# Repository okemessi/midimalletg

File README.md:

Wiki: https://github.com/okemessi/midimalletg/wiki

# midimalletg

Midimalletg is a MIDI mallet controller for marimba/other keyboard percussion players. This project is developed as a hobby and personal project by okemessi. It is provided as-is because it is still under development. 

## Specifications

Detailed specifications will be added to the wiki page (https://github.com/okemessi/midimalletg/wiki) as they become available.

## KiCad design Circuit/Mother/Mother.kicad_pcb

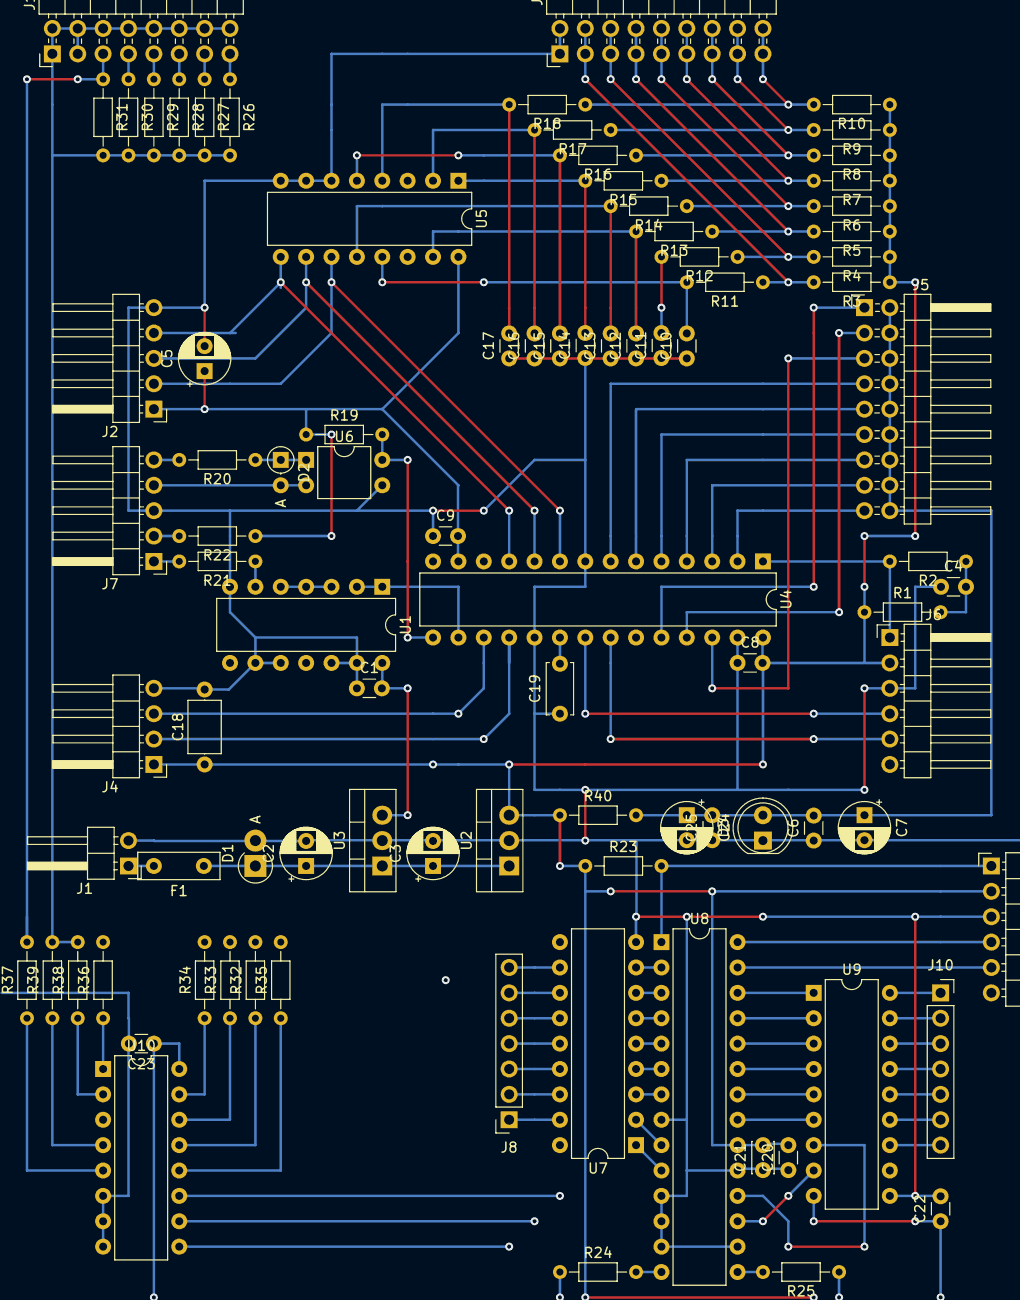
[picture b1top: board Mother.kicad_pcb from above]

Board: 4 copper layers, 90 parts (0 on the bottom side), 98 nets.

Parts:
C1, C4, C6, C8, C9, C10, C11, C12, C13, C14, C15, C16, C17, C20, C22, C23, C25: 0.1u; C_Disc_D3.0mm_W1.6mm_P2.50mm
C2, C3, C5, C7, C24: 10u; CP_Radial_D5.0mm_P2.50mm
C18: 10u; C_Axial_L5.1mm_D3.1mm_P7.50mm_Horizontal
C19: 10uF; C_Disc_D5.0mm_W2.5mm_P5.00mm
C21: 0.01u; C_Disc_D3.0mm_W2.0mm_P2.50mm
D1: 1N4007; D_DO-41_SOD81_P2.54mm_Vertical_AnodeUp
D2: 1SS178; D_DO-35_SOD27_P2.54mm_Vertical_AnodeUp
D3: LED; LED_D5.0mm
F1: RXEF050; C_Disc_D8.0mm_W2.5mm_P5.00mm
J1: Conn_01x02_Male; PinHeader_1x02_P2.54mm_Horizontal
J2, J7: Conn_01x05_Male; PinHeader_1x05_P2.54mm_Horizontal
J3, J5: Conn_02x09_Odd_Even; PinHeader_2x09_P2.54mm_Horizontal
J4: Conn_01x04_Male; PinHeader_1x04_P2.54mm_Horizontal
J6, J9: Conn_PIC_ICSP_ICD; PinHeader_1x06_P2.54mm_Horizontal
J8, J10: Conn_01x07_Female; PinSocket_1x07_P2.54mm_Vertical
J11: Conn_02x08_Odd_Even; PinHeader_2x08_P2.54mm_Horizontal
R1, R3, R4, R5, R6, R7, R8, R9, R10, R11, R12, R13, R14, R15, R16, R17, R18, R23: 10k; R_Axial_DIN0204_L3.6mm_D1.6mm_P7.62mm_Horizontal
R2, R40: 1k; R_Axial_DIN0204_L3.6mm_D1.6mm_P7.62mm_Horizontal
R19, R20, R21, R22, R32, R33, R34, R35, R36, R37, R38, R39: 220; R_Axial_DIN0204_L3.6mm_D1.6mm_P7.62mm_Horizontal
R24, R25: 4.7k; R_Axial_DIN0204_L3.6mm_D1.6mm_P7.62mm_Horizontal
R26, R27, R28, R29, R30, R31: 1Meg; R_Axial_DIN0204_L3.6mm_D1.6mm_P7.62mm_Horizontal
U1: 74HC00; DIP-14_W7.62mm
U2: BP5293-33; TO-220-3_Vertical
U3: BP5293-50; TO-220-3_Vertical
U4: PIC32MX110F016B-I_SP; DIP-28_W7.62mm
U5, U10: 4051; DIP-16_W7.62mm
U6: TLP785; DIP-4_W7.62mm
U7: ULN2803A; DIP-18_W7.62mm
U8: PIC16F18854-SO; DIP-28_W7.62mm
U9: TBD62783A; DIP-18_W7.62mm

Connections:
+5V: C1.2, U1.14, U3.3
/Sheet60D32BD3/SCL: J4.3, R24.2, U4.17, U8.14
/Sheet60D32BD3/SDA: J4.2, R25.2, U4.18, U8.15
/Sheet60E5A5FF/A: J2.2, U4.9, U5.11, U10.11
/Sheet60E5A5FF/A+: J5.3, U4.25, U10.3
/Sheet60E5A5FF/A-: C6.2, C7.1, C24.1, C25.2, D3.2, J5.2, J5.4, J5.6, J5.8, J5.10, J5.12, J5.14, J5.16, J5.18, J11.1, J11.2, J11.3, J11.4, J11.6, J11.8, J11.10, J11.12, J11.14, J11.16, R26.2, R27.2, R28.2, R29.2, R30.2, R31.2, R38.2, R39.2, R40.2
/Sheet60E5A5FF/B: J2.3, U4.10, U5.10, U10.10
/Sheet60E5A5FF/C: J2.4, U4.11, U5.9, U10.9
GND: C1.1, C2.2, C3.2, C4.1, C5.2, C6.1, C7.2, C8.1, C9.1, C10.1, C11.1, C12.1, C13.1, C14.1, C15.1, C16.1, C17.1, C18.2, C19.1, C20.1, C21.1, C22.2, C23.2, C24.2, C25.1, D1.2, D3.1, J1.2, J2.5, J3.1, J3.2, J4.4, J6.3, J7.3, J9.3, U1.7, U1.9, U1.10, U1.12, U1.13, U2.2, U3.2, U4.8, U4.19, U4.27, U5.6, U5.7, U5.8, U6.3, U7.9, U8.8, U8.11, U8.12, U8.13, U8.16, U8.19, U9.10, U10.6, U10.7, U10.8
unnamed: C2.1, C3.1, D1.1, F1.1, U2.1, U3.1
unnamed: C4.2, R1.2, R2.1
unnamed: C10.2, R11.2, U5.13
unnamed: C11.2, R12.2, U5.14
unnamed: C12.2, R13.2, U5.15
unnamed: C13.2, R14.2, U5.12
unnamed: C14.2, R15.2, U5.1
unnamed: C15.2, R16.2, U5.5
unnamed: C16.2, R17.2, U5.2
unnamed: C17.2, R18.2, U5.4
unnamed: C19.2, U4.20
unnamed: D2.1, R20.1, U6.1
unnamed: D2.2, J7.4, U6.2
unnamed: F1.2, J1.1
unnamed: J3.3, J3.4, R3.2, R11.1
unnamed: J3.5, J3.6, R4.2, R12.1
unnamed: J3.7, J3.8, R5.2, R13.1
unnamed: J3.9, J3.10, R6.2, R14.1
unnamed: J3.11, J3.12, R7.2, R15.1
unnamed: J3.13, J3.14, R8.2, R16.1
unnamed: J3.15, J3.16, R9.2, R17.1
unnamed: J3.17, J3.18, R10.2, R18.1
unnamed: J5.1, U4.24
unnamed: J5.5, U4.26
unnamed: J5.7, U4.7
unnamed: J5.9, U4.6
unnamed: J5.11, U4.5
unnamed: J5.13, U4.4
unnamed: J5.15, U4.3
unnamed: J5.17, U4.2
unnamed: J6.1, R2.2, U4.1
unnamed: J6.4, U4.21
unnamed: J6.5, U4.22
unnamed: J7.1, R21.2
unnamed: J7.2, R22.2
unnamed: J7.5, R20.2
unnamed: J8.1, U7.17
unnamed: J8.2, U7.16
unnamed: J8.3, U7.15
unnamed: J8.4, U7.14
unnamed: J8.5, U7.13
unnamed: J8.6, U7.12
unnamed: J8.7, U7.11
unnamed: J9.1, R23.2, U8.1
unnamed: J9.4, U8.28
unnamed: J9.5, U8.27
unnamed: J10.1, U9.18
unnamed: J10.2, U9.17
unnamed: J10.3, U9.16
unnamed: J10.4, U9.15
unnamed: J10.5, U9.14
unnamed: J10.6, U9.13
unnamed: J10.7, U9.12
unnamed: J11.5, R31.1, R37.2
unnamed: J11.7, R30.1, R36.2
unnamed: J11.9, R29.1, R35.2
unnamed: J11.11, R28.1, R34.2
unnamed: J11.13, R27.1, R33.2
unnamed: J11.15, R26.1, R32.2
unnamed: R19.2, U4.15, U6.4
unnamed: R21.1, U1.6
unnamed: R32.1, U10.13
unnamed: R33.1, U10.14
unnamed: R34.1, U10.15
unnamed: R35.1, U10.12
unnamed: R36.1, U10.1
unnamed: R37.1, U10.5
unnamed: R38.1, U10.2
unnamed: R39.1, U10.4
unnamed: U1.1, U1.2, U4.16
unnamed: U1.3, U1.4, U1.5
unnamed: U4.23, U5.3
unnamed: U7.1, U8.10
unnamed: U7.2, U8.9
unnamed: U7.3, U8.7
unnamed: U7.4, U8.6
unnamed: U7.5, U8.5
unnamed: U7.6, U8.4
unnamed: U7.7, U8.3
unnamed: U7.8, U8.2
unnamed: U8.17, U9.8
unnamed: U8.18, U9.7
unnamed: U8.21, U9.6
unnamed: U8.22, U9.5
unnamed: U8.23, U9.4
unnamed: U8.24, U9.3
unnamed: U8.25, U9.2
unnamed: U8.26, U9.1
VDD: C5.1, C8.2, C9.2, C18.1, C20.2, C21.2, C22.1, C23.1, J2.1, J4.1, J6.2, J9.2, R1.1, R3.1, R4.1, R5.1, R6.1, R7.1, R8.1, R9.1, R10.1, R19.1, R22.1, R23.1, R24.1, R25.1, R40.1, U2.3, U4.13, U4.28, U5.16, U8.20, U9.9, U10.16

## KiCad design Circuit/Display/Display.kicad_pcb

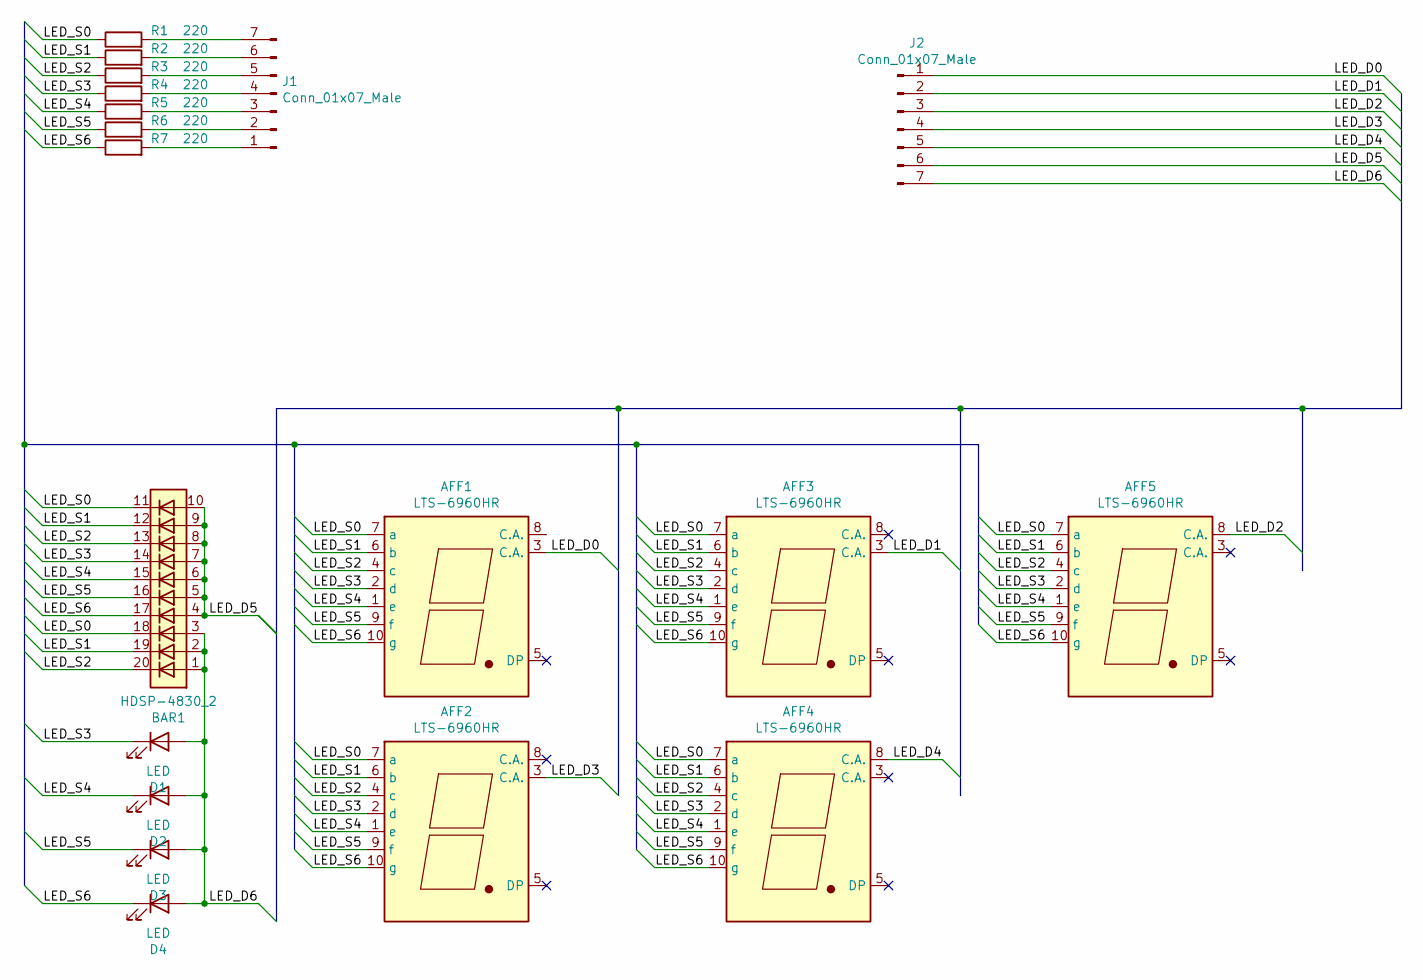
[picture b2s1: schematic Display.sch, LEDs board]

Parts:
AFF1, AFF2, AFF3, AFF4, AFF5: LTS-6960HR; 7SegmentLED_LTS6760_LTS6780
BAR1: HDSP-4830_2; HDSP-4830
D1, D2, D3, D4: LED; LED_D3.0mm
J1, J2: Conn_01x07_Male; PinHeader_1x07_P2.54mm_Vertical
R1, R2, R3, R4, R5, R6, R7: 220; R_Axial_DIN0204_L3.6mm_D1.6mm_P7.62mm_Horizontal

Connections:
/LED_D0: AFF1.3 (C.A.), J2.1
/LED_D1: AFF3.3 (C.A.), J2.2
/LED_D2: AFF5.8 (C.A.), J2.3
/LED_D3: AFF2.3 (C.A.), J2.4
/LED_D4: AFF4.8 (C.A.), J2.5
/LED_D5: BAR1.4 (A), BAR1.5 (A), BAR1.6 (A), BAR1.7 (A), BAR1.8 (A), BAR1.9 (A), BAR1.10 (A), J2.6
/LED_D6: BAR1.1 (A), BAR1.2 (A), BAR1.3 (A), D1.2 (A), D2.2 (A), D3.2 (A), D4.2 (A), J2.7
/LED_S0: AFF1.7 (a), AFF2.7 (a), AFF3.7 (a), AFF4.7 (a), AFF5.7 (a), BAR1.11 (K), BAR1.18 (K), R1.1
/LED_S1: AFF1.6 (b), AFF2.6 (b), AFF3.6 (b), AFF4.6 (b), AFF5.6 (b), BAR1.12 (K), BAR1.19 (K), R2.1
/LED_S2: AFF1.4 (c), AFF2.4 (c), AFF3.4 (c), AFF4.4 (c), AFF5.4 (c), BAR1.13 (K), BAR1.20 (K), R3.1
/LED_S3: AFF1.2 (d), AFF2.2 (d), AFF3.2 (d), AFF4.2 (d), AFF5.2 (d), BAR1.14 (K), D1.1 (K), R4.1
/LED_S4: AFF1.1 (e), AFF2.1 (e), AFF3.1 (e), AFF4.1 (e), AFF5.1 (e), BAR1.15 (K), D2.1 (K), R5.1
/LED_S5: AFF1.9 (f), AFF2.9 (f), AFF3.9 (f), AFF4.9 (f), AFF5.9 (f), BAR1.16 (K), D3.1 (K), R6.1
/LED_S6: AFF1.10 (g), AFF2.10 (g), AFF3.10 (g), AFF4.10 (g), AFF5.10 (g), BAR1.17 (K), D4.1 (K), R7.1
unnamed: J1.1, R7.2
unnamed: J1.2, R6.2
unnamed: J1.3, R5.2
unnamed: J1.4, R4.2
unnamed: J1.5, R3.2
unnamed: J1.6, R2.2
unnamed: J1.7, R1.2

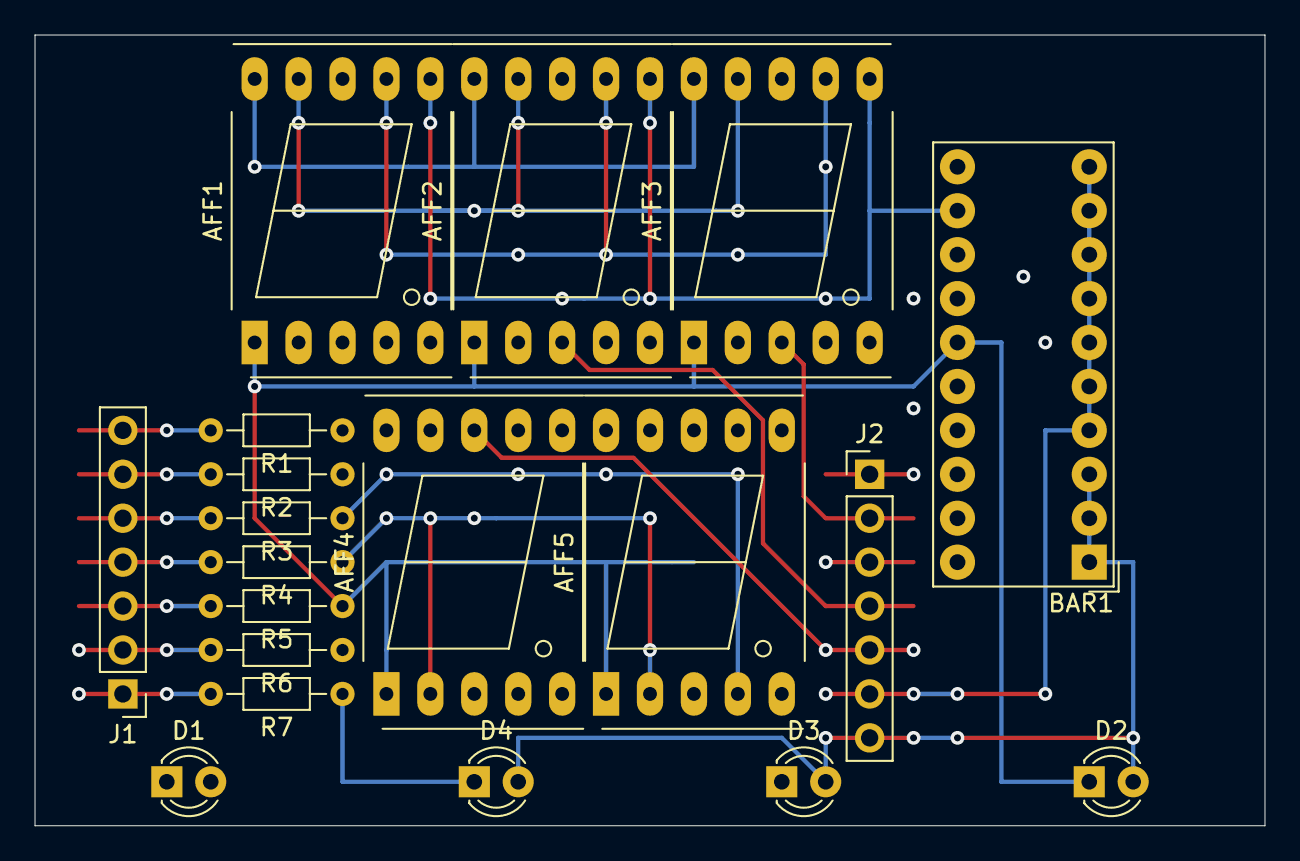
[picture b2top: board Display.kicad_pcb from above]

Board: 4 copper layers, 71.1 x 45.7 mm, 19 parts (0 on the bottom side), 21 nets.

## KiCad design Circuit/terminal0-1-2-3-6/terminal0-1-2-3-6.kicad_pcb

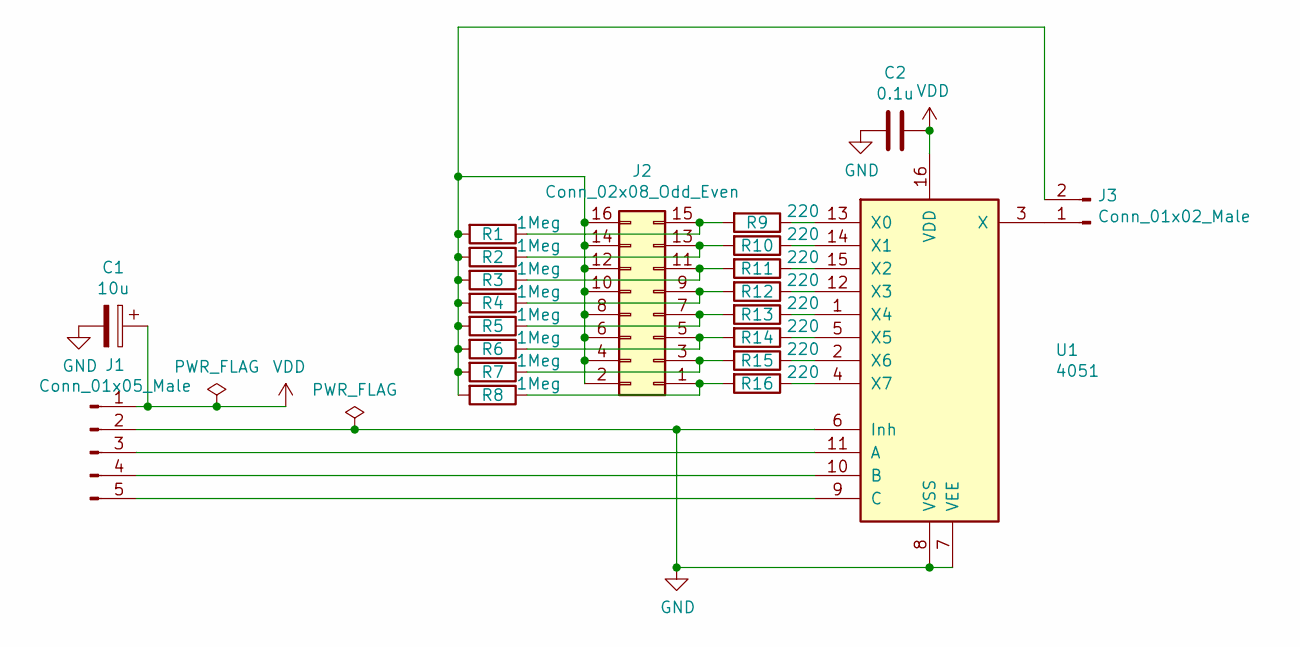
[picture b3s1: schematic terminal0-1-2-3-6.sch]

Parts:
C1: 10u; CP_Radial_D5.0mm_P2.50mm
C2: 0.1u; C_Disc_D3.0mm_W1.6mm_P2.50mm
J1: Conn_01x05_Male; PinHeader_1x05_P2.54mm_Horizontal
J2: Conn_02x08_Odd_Even; PinHeader_2x08_P2.54mm_Horizontal
J3: Conn_01x02_Male; PinHeader_1x02_P2.54mm_Horizontal
R1, R2, R3, R4, R5, R6, R7, R8: 1Meg; R_Axial_DIN0204_L3.6mm_D1.6mm_P7.62mm_Horizontal
R9, R10, R11, R12, R13, R14, R15, R16: 220; R_Axial_DIN0204_L3.6mm_D1.6mm_P7.62mm_Horizontal
U1: 4051; DIP-16_W7.62mm

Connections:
GND: C1.2, C2.2, J1.2, U1.6 (Inh), U1.7 (VEE), U1.8 (VSS)
unnamed: J1.3, U1.11 (A)
unnamed: J1.4, U1.10 (B)
unnamed: J1.5, U1.9 (C)
unnamed: J2.1, R8.1, R16.2
unnamed: J2.3, R7.1, R15.2
unnamed: J2.5, R6.1, R14.2
unnamed: J2.7, R5.1, R13.2
unnamed: J2.9, R4.1, R12.2
unnamed: J2.2, J2.4, J2.6, J2.8, J2.10, J2.12, J2.14, J2.16, J3.2, R1.2, R2.2, R3.2, R4.2, R5.2, R6.2, R7.2, R8.2
unnamed: J2.11, R3.1, R11.2
unnamed: J2.13, R2.1, R10.2
unnamed: J2.15, R1.1, R9.2
unnamed: J3.1, U1.3 (X)
unnamed: R9.1, U1.13 (X0)
unnamed: R10.1, U1.14 (X1)
unnamed: R11.1, U1.15 (X2)
unnamed: R12.1, U1.12 (X3)
unnamed: R13.1, U1.1 (X4)
unnamed: R14.1, U1.5 (X5)
unnamed: R15.1, U1.2 (X6)
unnamed: R16.1, U1.4 (X7)
VDD: C1.1, C2.1, J1.1, U1.16 (VDD)

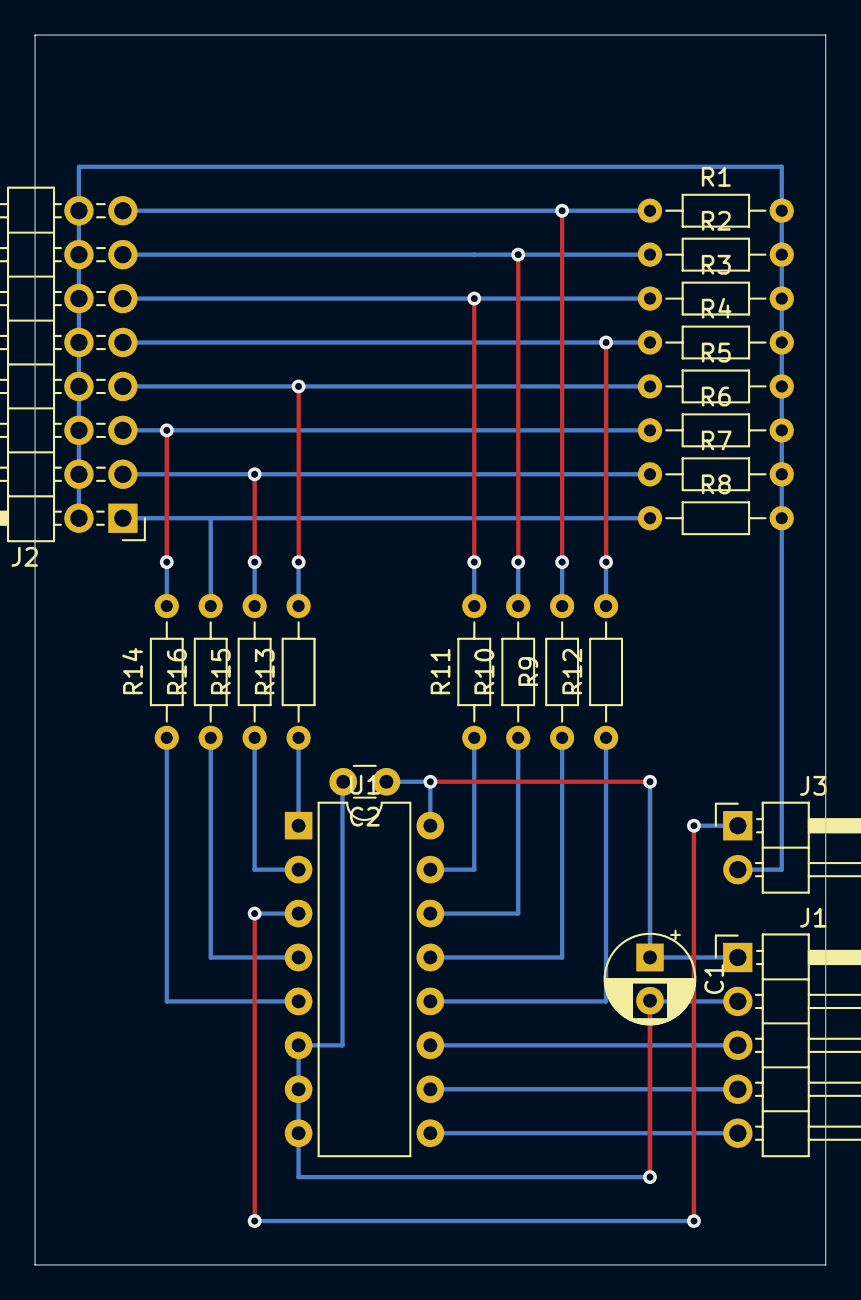
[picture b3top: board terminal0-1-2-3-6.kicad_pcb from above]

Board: 2 copper layers, 45.7 x 71.1 mm, 22 parts (0 on the bottom side), 23 nets.

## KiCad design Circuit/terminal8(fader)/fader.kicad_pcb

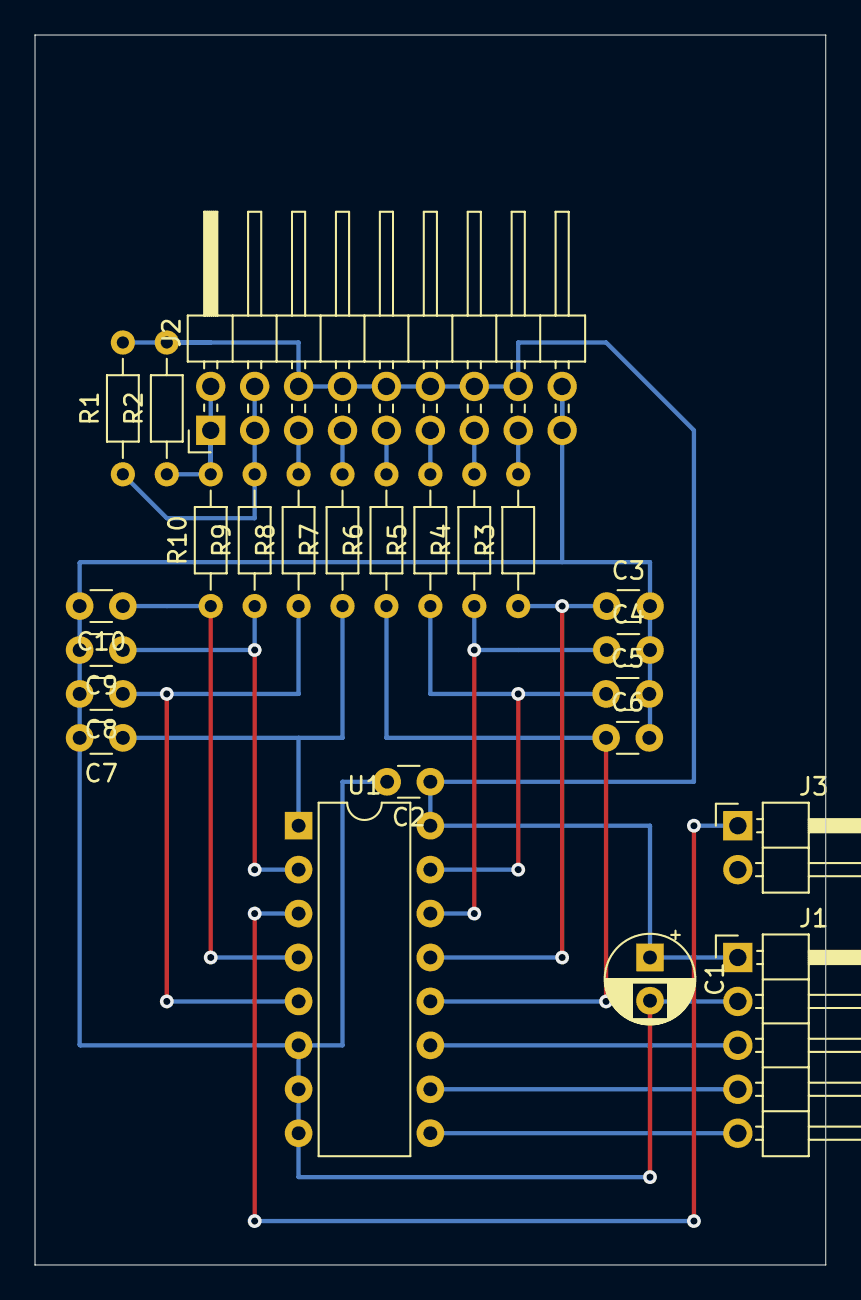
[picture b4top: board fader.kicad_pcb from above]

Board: 2 copper layers, 45.7 x 71.1 mm, 24 parts (0 on the bottom side), 22 nets.

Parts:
C1: 10u; CP_Radial_D5.0mm_P2.50mm
C2, C3, C4, C5, C6, C7, C8, C9, C10: 0.1u; C_Disc_D3.0mm_W1.6mm_P2.50mm
J1: Conn_01x05_Male; PinHeader_1x05_P2.54mm_Horizontal
J2: 0.1u; PinHeader_2x09_P2.54mm_Horizontal
J3: Conn_01x02_Male; PinHeader_1x02_P2.54mm_Horizontal
R1, R2, R3, R4, R5, R6, R7, R8, R9, R10: 10k; R_Axial_DIN0204_L3.6mm_D1.6mm_P7.62mm_Horizontal
U1: 4051; DIP-16_W7.62mm

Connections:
GND: C1.2, C2.2, C3.2, C4.2, C5.2, C6.2, C7.2, C8.2, C9.2, C10.2, J1.2, J2.17, J2.18, U1.6, U1.7, U1.8
unnamed: C3.1, R3.1, U1.13
unnamed: C4.1, R4.1, U1.14
unnamed: C5.1, R5.1, U1.15
unnamed: C6.1, R6.1, U1.12
unnamed: C7.1, R7.1, U1.1
unnamed: C8.1, R8.1, U1.5
unnamed: C9.1, R9.1, U1.2
unnamed: C10.1, R10.1, U1.4
unnamed: J1.3, U1.11
unnamed: J1.4, U1.10
unnamed: J1.5, U1.9
unnamed: J2.1, J2.2, R2.1, R10.2
unnamed: J2.3, J2.4, R1.1, R9.2
unnamed: J2.5, R8.2
unnamed: J2.7, R7.2
unnamed: J2.9, R6.2
unnamed: J2.11, R5.2
unnamed: J2.13, R4.2
unnamed: J2.15, R3.2
unnamed: J3.1, U1.3
VDD: C1.1, C2.1, J1.1, J2.6, J2.8, J2.10, J2.12, J2.14, J2.16, R1.2, R2.2, U1.16

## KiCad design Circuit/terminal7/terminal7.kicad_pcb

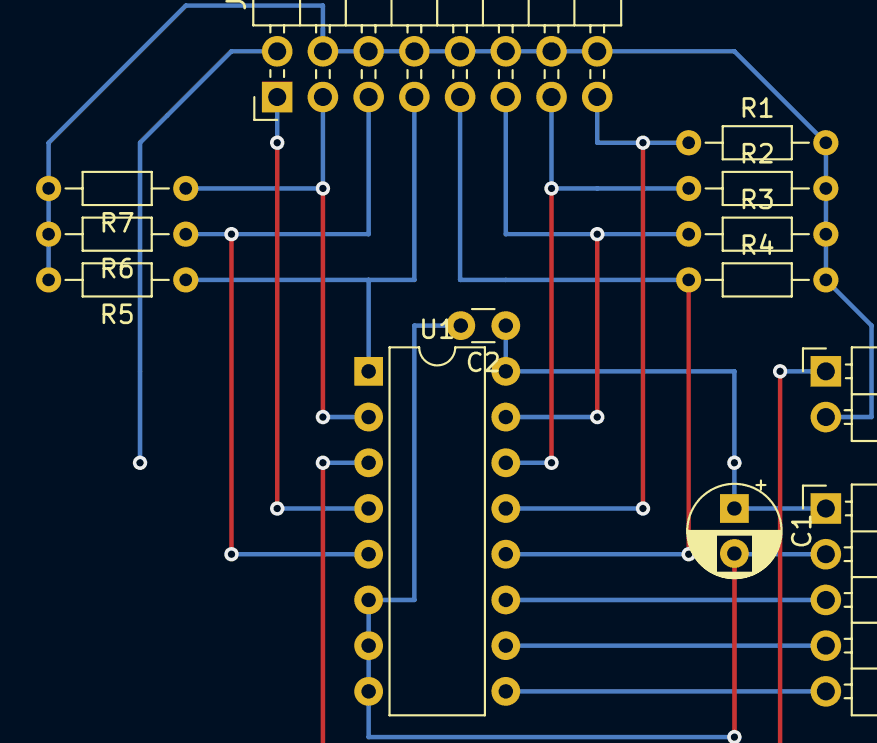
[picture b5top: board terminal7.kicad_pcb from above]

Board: 4 copper layers, 13 parts (0 on the bottom side), 15 nets.

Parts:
C1: 10u; CP_Radial_D5.0mm_P2.50mm
C2: 0.1u; C_Disc_D3.0mm_W1.6mm_P2.50mm
J1: Conn_01x05_Male; PinHeader_1x05_P2.54mm_Horizontal
J2: Conn_02x08_Odd_Even; PinHeader_2x08_P2.54mm_Horizontal
J3: Conn_01x02_Male; PinHeader_1x02_P2.54mm_Horizontal
R1, R2, R3, R4, R5, R6: 1Meg; R_Axial_DIN0204_L3.6mm_D1.6mm_P7.62mm_Horizontal
R7: 10k; R_Axial_DIN0204_L3.6mm_D1.6mm_P7.62mm_Horizontal
U1: 4051; DIP-16_W7.62mm

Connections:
GND: C1.2, C2.2, J1.2, U1.6, U1.7, U1.8
unnamed: J1.3, U1.11
unnamed: J1.4, U1.10
unnamed: J1.5, U1.9
unnamed: J2.1, U1.4
unnamed: J2.3, R7.1, U1.2
unnamed: J2.5, R6.1, U1.5
unnamed: J2.7, R5.1, U1.1
unnamed: J2.9, R4.1, U1.12
unnamed: J2.4, J2.6, J2.8, J2.10, J2.12, J2.14, J2.16, J3.2, R1.2, R2.2, R3.2, R4.2, R5.2, R6.2, R7.2
unnamed: J2.11, R3.1, U1.15
unnamed: J2.13, R2.1, U1.14
unnamed: J2.15, R1.1, U1.13
unnamed: J3.1, U1.3
VDD: C1.1, C2.1, J1.1, J2.2, U1.16

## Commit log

2020-08-08 Update LICENSE
    GPLv2
2020-08-09 block diagram, region map, gitignore(dia~)
2020-08-09 add hardware picture
2020-08-09 picture editted
2020-08-09 Change region for 28-pin MCUs
2020-08-09 Revert "Change region for 28-pin MCUs"
    This reverts commit 3ff99377e96ba2532b7dffdd28af3aaaafb2cf97.
2020-08-10 Add note numbers, mod for 28pin-only nodes
2020-08-10 region data collection
2020-08-10 Directorize
2020-08-19 MCC configuration
2020-08-19 chip #3 first build: success
2020-08-19 #3 changed conditions for sending message
2020-08-19 #1 mcc
2020-08-19 #1 first build: successful
2020-08-19 #1 changed pin assign
2020-08-19 #4 first build: successful
2020-08-19 #2 first build: successful
2020-08-19 #2 first build successful
2020-08-19 updated chip id
2020-08-19 #5 first build: succeeded
2020-08-19 #0 first build: succeeded
2020-08-19 !bug fix of & and |
2020-08-20 chipF mcc + chip0 bug fix
2020-08-21 bug fix: send message condition
    if (scan_max[i]>0 && scan_max_prev[i]!=scan_max[i])
    →if (scan_max_prev[i]!=scan_max[i])
2020-09-02 32bit initial commit
2020-09-04 bug fix: switch polarity
2020-09-04 added MCUs pin assign
2020-09-05 3se(initial)
2020-09-06 updated hardware (controll panel)
2020-09-06 extended numbers of faders and buttons
2020-09-06 switch polarity detection added
2020-09-07 8bit circuit (chip#0-5) complete
2020-12-13 eeprom
2020-12-19 first build
2021-02-15 2021/02/15作業再開
2021-02-17 circuit
2021-02-17 display
2021-02-23 20200223
2021-02-23 端末全完成
2021-02-25 Display分割
2021-02-25 terminal5
2021-02-25 mother回路図作成
2021-02-26 基板完成
2021-03-04 ECM対策
2021-03-04 回路系全完成
2021-03-10 回路完成
2021-06-04 20210604
2021-06-11 メイン飛んだ
2021-06-11 メインボード実装完了
2021-06-11 ディスプレイ単独テスト完了
2021-08-03 displayにi2c搭載
